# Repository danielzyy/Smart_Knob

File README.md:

# Smart_Knob
A multifunctional smart knob capable of simulating haptic feedback using a BLDC motor.

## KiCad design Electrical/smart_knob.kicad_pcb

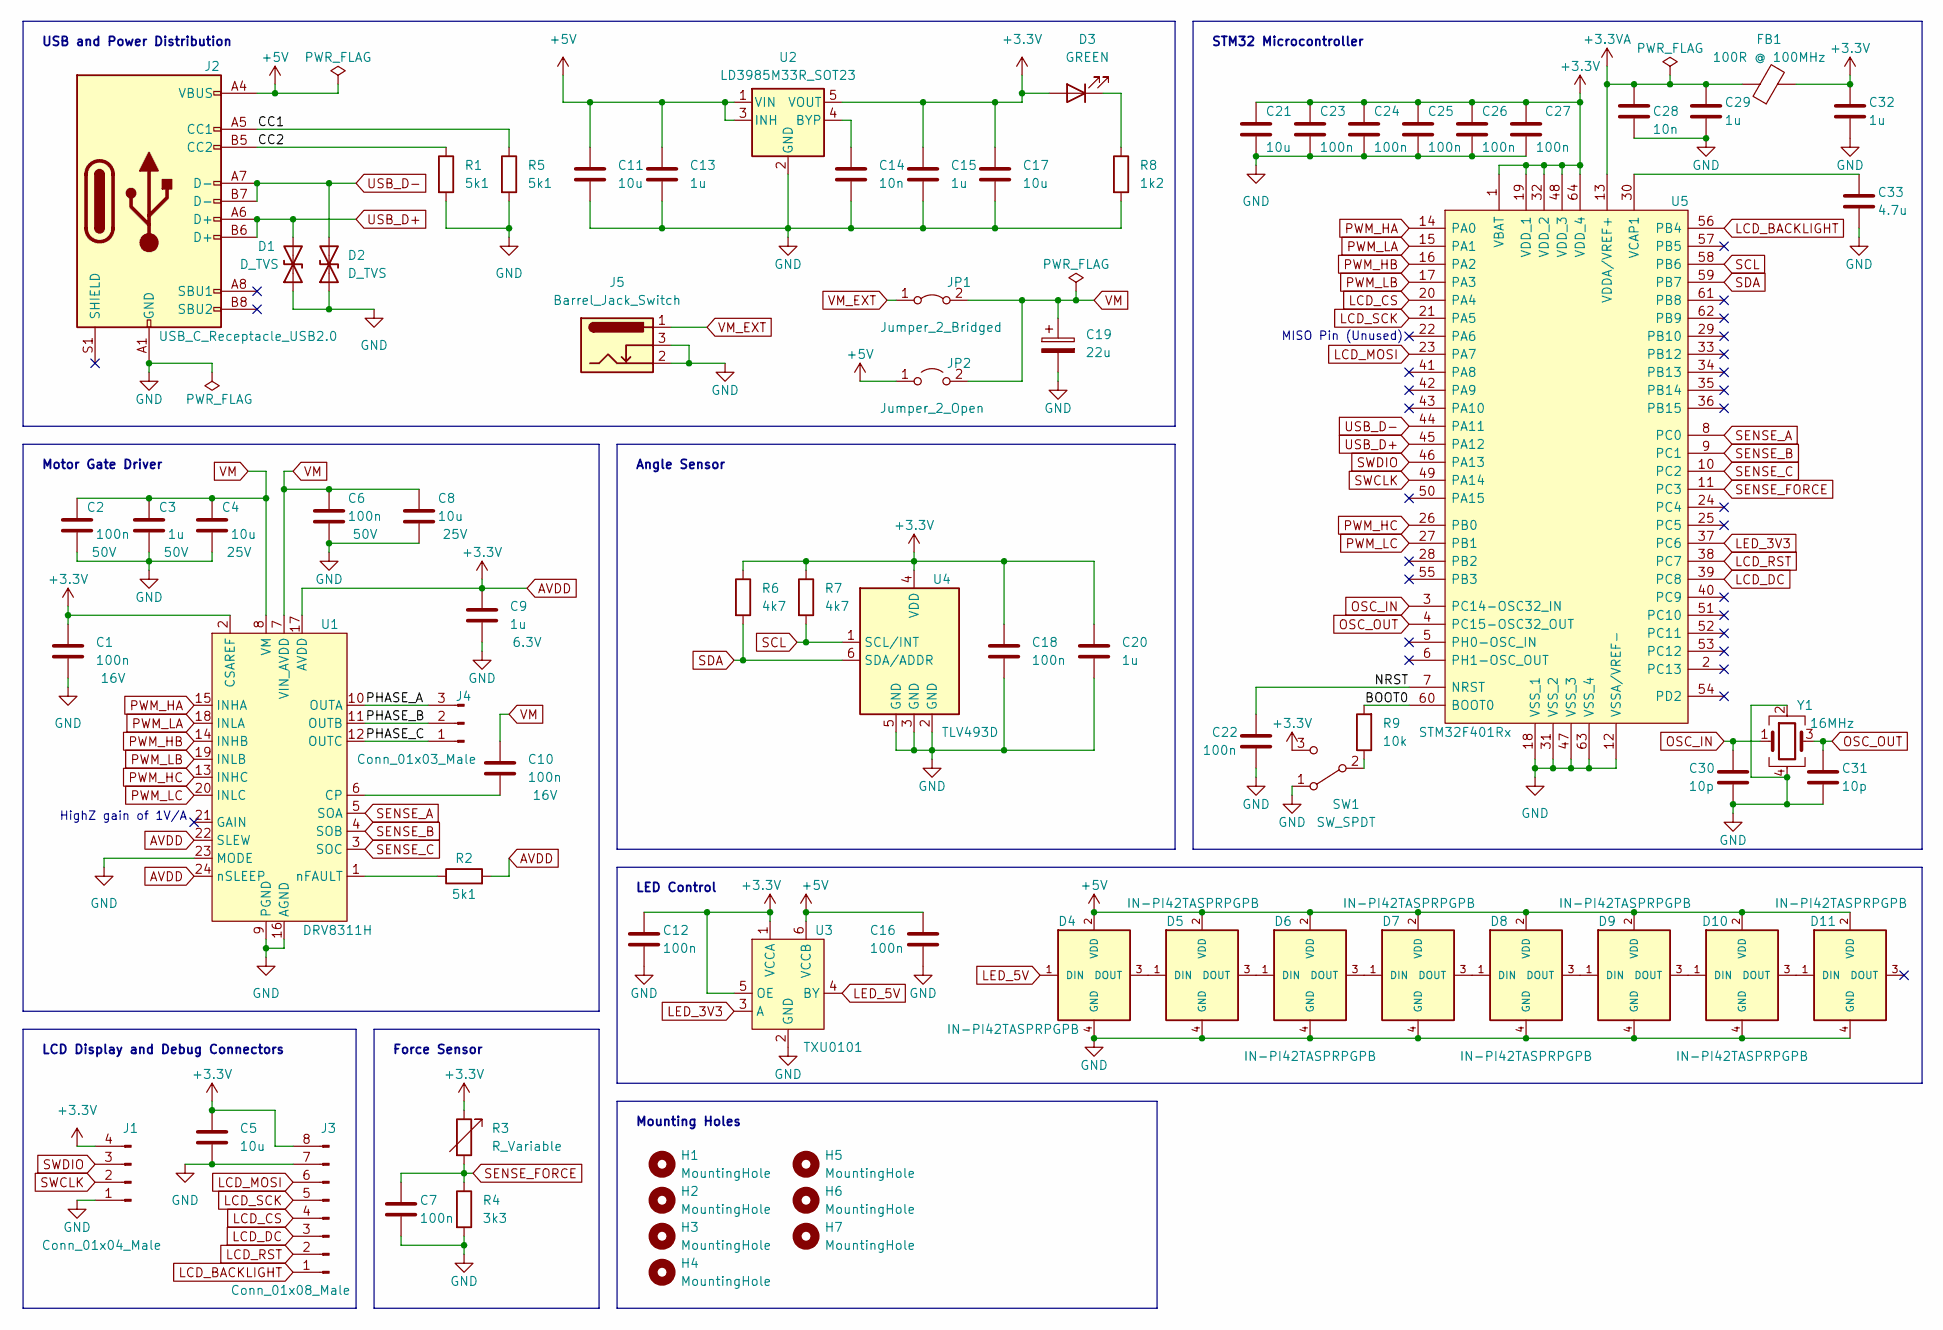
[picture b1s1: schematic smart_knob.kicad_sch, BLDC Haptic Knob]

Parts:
C1, C10: 100n; C_0603_1608Metric; Rating 16V
C2, C6: 100n; C_0603_1608Metric; Rating 50V
C3: 1u; C_0603_1608Metric; Rating 50V
C4, C8: 10u; C_0603_1608Metric; Rating 25V
C5, C11, C17, C21: 10u; C_0603_1608Metric
C7, C12, C16, C18, C22, C23, C24, C25, C26, C27: 100n; C_0603_1608Metric
C9: 1u; C_0603_1608Metric; Rating 6.3V
C13, C15, C20, C29, C32: 1u; C_0603_1608Metric
C14, C28: 10n; C_0603_1608Metric
C19: 22u; CP_EIA-2012-12_Kemet-R
C30, C31: 10p; C_0603_1608Metric
C33: 4.7u; C_0603_1608Metric
D1, D2: D_TVS; D_0603_1608Metric
D3: GREEN; LED_0603_1608Metric
D4, D5, D6, D7, D8, D9, D10, D11: IN-PI42TASPRPGPB; LED_IN-PI42TASPRPGPB; PARTREV Oct. 10, 2021
FB1: 100R @ 100MHz; L_0603_1608Metric
H1, H2, H3, H4, H5, H6, H7: MountingHole; MountingHole_1.8mm_M1.6
J1: Conn_01x04_Male; PinHeader_1x04_P2.54mm_Horizontal
J2: USB_C_Receptacle_USB2.0; GCT_USB4110-GF-A_REVB_USB2.0
J3: Conn_01x08_Male; LCD_Display
J4: Conn_01x03_Male; Molex_PicoBlade_53261-0371_1x03-1MP_P1.25mm_Horizontal
J5: Barrel_Jack_Switch; TENSILITY_54-00127
JP1: Jumper_2_Bridged; R_0603_1608Metric
JP2: Jumper_2_Open; R_0603_1608Metric
R1, R2, R5: 5k1; R_0603_1608Metric
R3: R_Variable; Force_Sensor
R4: 3k3; R_0603_1608Metric
R6, R7: 4k7; R_0603_1608Metric
R8: 1k2; R_0603_1608Metric
R9: 10k; R_0603_1608Metric
SW1: SW_SPDT; SW_SPDT_CK-JS102011SAQN
U1: DRV8311H; WQFN-24-3x3mm
U2: LD3985M33R_SOT23; SOT-23-5
U3: TXU0101; TXU0101DCKR
U4: TLV493D; SOT-23-6
U5: STM32F401Rx; QFP50P1200X1200X160-64N; Manufacturer_Part_Number STM32F401RET6; Mouser Part Number 511-STM32F401RET6
Y1: 16MHz; Crystal_SMD_Abracon_ABM8G-4Pin_3.2x2.5mm

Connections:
+3.3VA: C28.1, C29.1, FB1.1, U5.13 (VDDA/VREF+)
+5V: C11.1, C13.1, C16.2, D4.2 (VDD), D5.2 (VDD), D6.2 (VDD), D7.2 (VDD), D8.2 (VDD), D9.2 (VDD), D10.2 (VDD), D11.2 (VDD), J2.A4 (VBUS), JP2.1 (A), U2.1 (VIN), U2.3 (INH), U3.6 (VCCB)
/BOOT0: R9.2, U5.60 (BOOT0)
/CC1: J2.A5 (CC1), R5.1
/CC2: J2.B5 (CC2), R1.1
/NRST: C22.1, U5.7 (NRST)
/PHASE_A: J4.3, U1.10 (OUTA)
/PHASE_B: J4.2, U1.11 (OUTB)
/PHASE_C: J4.1, U1.12 (OUTC)
AVDD: C1.1, C5.1, C9.1, C12.2, C15.1, C17.1, C18.1, C20.1, C21.1, C23.1, C24.1, C25.1, C26.1, C27.1, C32.1, D3.2 (A), FB1.2, J1.4, J3.8, R2.2, R3.1, R6.1, R7.1, SW1.3 (C), U1.2 (CSAREF), U1.17 (AVDD), U1.22 (SLEW), U1.24 (nSLEEP), U2.5 (VOUT), U3.1 (VCCA), U3.5 (OE), U4.4 (VDD), U5.1 (VBAT), U5.19 (VDD_1), U5.32 (VDD_2), U5.48 (VDD_3), U5.64 (VDD_4)
GND: C1.2, C2.1, C3.2, C4.2, C5.2, C6.1, C7.2, C8.2, C9.2, C11.2, C12.1, C13.2, C14.2, C15.2, C16.1, C17.2, C18.2, C19.2, C20.2, C21.2, C22.2, C23.2, C24.2, C25.2, C26.2, C27.2, C28.2, C29.2, C30.2, C31.2, C32.2, C33.2, D1.1 (A1), D2.1 (A1), D4.4 (GND), D5.4 (GND), D6.4 (GND), D7.4 (GND), D8.4 (GND), D9.4 (GND), D10.4 (GND), D11.4 (GND), J1.1, J2.A1 (GND), J3.7, J5.2, J5.3, R1.2, R4.2, R5.2, R8.2, SW1.1 (A), U1.9 (PGND), U1.16 (AGND), U1.23 (MODE), U2.2 (GND), U3.2 (GND), U4.2 (GND), U4.3 (GND), U4.5 (GND), U5.12 (VSSA/VREF-), U5.18 (VSS_1), U5.31 (VSS_2), U5.47 (VSS_3), U5.63 (VSS_4), Y1.2, Y1.4
LCD_BACKLIGHT: J3.1, U5.56 (PB4)
LCD_CS: J3.4, U5.20 (PA4)
LCD_DC: J3.3, U5.39 (PC8)
LCD_MOSI: J3.6, U5.23 (PA7)
LCD_RST: J3.2, U5.38 (PC7)
LCD_SCK: J3.5, U5.21 (PA5)
LED_3V3: U3.3 (A), U5.37 (PC6)
LED_5V: D4.1 (DIN), U3.4 (BY)
unnamed: D3.1 (K), R8.1
unnamed: D4.3 (DOUT), D5.1 (DIN)
unnamed: D5.3 (DOUT), D6.1 (DIN)
unnamed: D6.3 (DOUT), D7.1 (DIN)
unnamed: D7.3 (DOUT), D8.1 (DIN)
unnamed: D8.3 (DOUT), D9.1 (DIN)
unnamed: D9.3 (DOUT), D10.1 (DIN)
unnamed: D10.3 (DOUT), D11.1 (DIN)
unnamed: R9.1, SW1.2 (B)
unnamed: C10.1, U1.6 (CP)
unnamed: R2.1, U1.1 (nFAULT)
unnamed: C14.1, U2.4 (BYP)
unnamed: C33.1, U5.30 (VCAP1)
OSC_IN: C30.1, U5.3 (PC14-OSC32_IN), Y1.1
OSC_OUT: C31.1, U5.4 (PC15-OSC32_OUT), Y1.3
PWM_HA: U1.15 (INHA), U5.14 (PA0)
PWM_HB: U1.14 (INHB), U5.16 (PA2)
PWM_HC: U1.13 (INHC), U5.26 (PB0)
PWM_LA: U1.18 (INLA), U5.15 (PA1)
PWM_LB: U1.19 (INLB), U5.17 (PA3)
PWM_LC: U1.20 (INLC), U5.27 (PB1)
SCL: R7.2, U4.1 (SCL/INT), U5.58 (PB6)
SDA: R6.2, U4.6 (SDA/ADDR), U5.59 (PB7)
SENSE_A: U1.5 (SOA), U5.8 (PC0)
SENSE_B: U1.4 (SOB), U5.9 (PC1)
SENSE_C: U1.3 (SOC), U5.10 (PC2)
SENSE_FORCE: C7.1, R3.2, R4.1, U5.11 (PC3)
SWCLK: J1.2, U5.49 (PA14)
SWDIO: J1.3, U5.46 (PA13)
USB_D+: D1.2 (A2), J2.A6 (D+), J2.B6 (D+), U5.45 (PA12)
USB_D-: D2.2 (A2), J2.A7 (D-), J2.B7 (D-), U5.44 (PA11)
VM: C2.2, C3.1, C4.1, C6.2, C8.1, C10.2, C19.1, JP1.2 (B), JP2.2 (B), U1.7 (VIN_AVDD), U1.8 (VM)
VM_EXT: J5.1, JP1.1 (A)

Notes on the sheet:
MISO Pin (Unused)
Mounting Holes
LCD Display and Debug Connectors
USB and Power Distribution
Force Sensor
LED Control
HighZ gain of 1V/A
STM32 Microcontroller
Angle Sensor
Motor Gate Driver

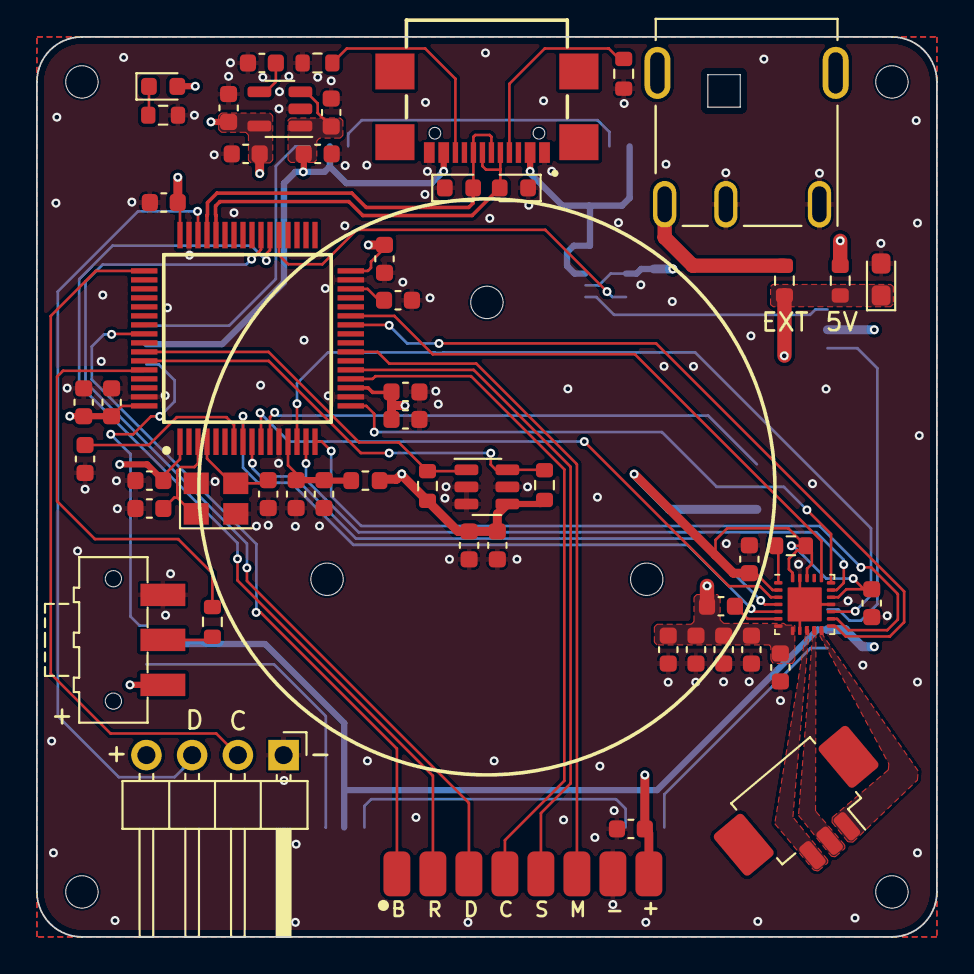
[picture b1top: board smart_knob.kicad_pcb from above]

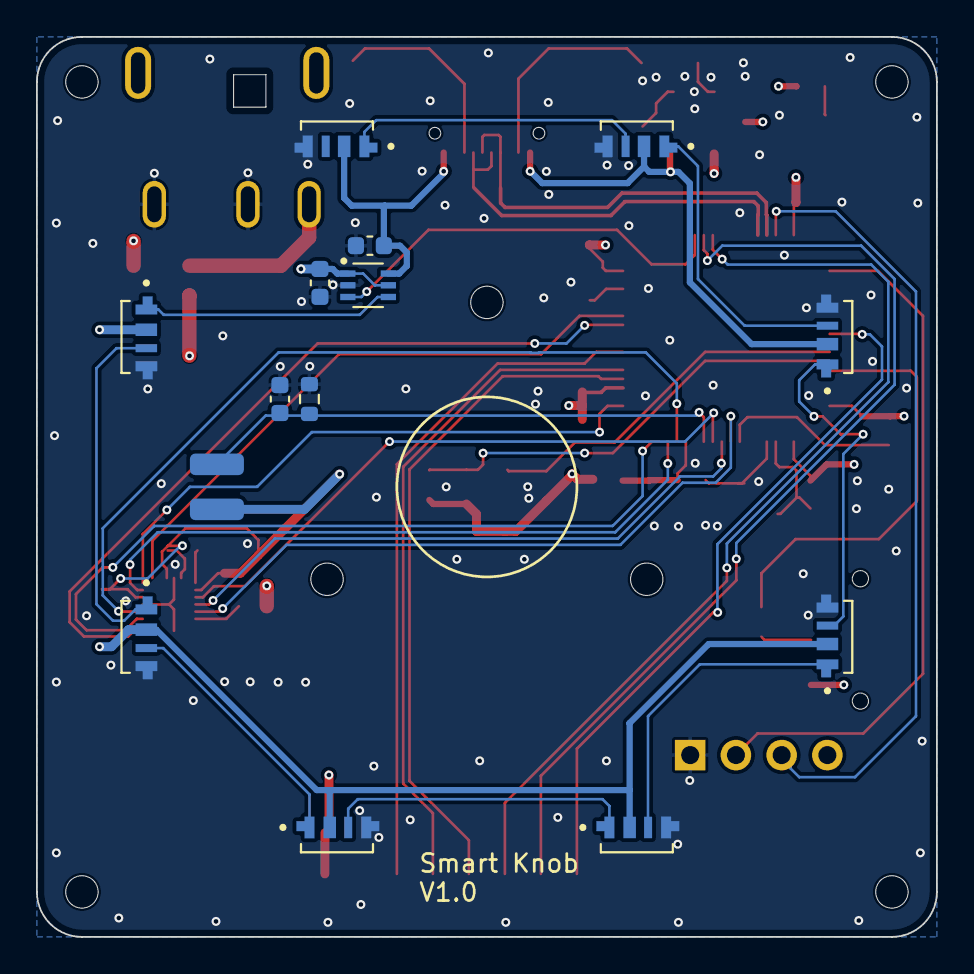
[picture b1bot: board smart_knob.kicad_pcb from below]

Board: 4 copper layers, 50.0 x 50.0 mm, 75 parts (14 on the bottom side), 52 nets.

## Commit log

2024-01-05 initial upload
2025-01-01 fix i2c crash preventing usb input
2025-01-01 fix schematic rework issues
2025-01-01 pcb interactive bom for assembly
